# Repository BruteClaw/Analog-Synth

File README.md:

# Analog-Synth
Analog Synthasizer Designs

These are designs for EuroRack compatable synthasizer modules.

Each module is designed as a seperate project in KiCAD
Each folder includes a BOM from Mouser.com, the Gerber Files if you just want to have a board printed and a PDF of the schematic.

I have taken insparation from all over the web including Music From Outer Space, Yusynth and Look Mom no Computer.
Some designs are outright copies of their schematic with my board layout design.

Look in Overal Design.xlsx for where I have gotten the design from And current progress on the designs.

All designs are without waranty, please build at your own risk, I have not tested any of these designs at this time.
If you build any of them, you assume responsibiltiy for any potential damage to your existing equipment.

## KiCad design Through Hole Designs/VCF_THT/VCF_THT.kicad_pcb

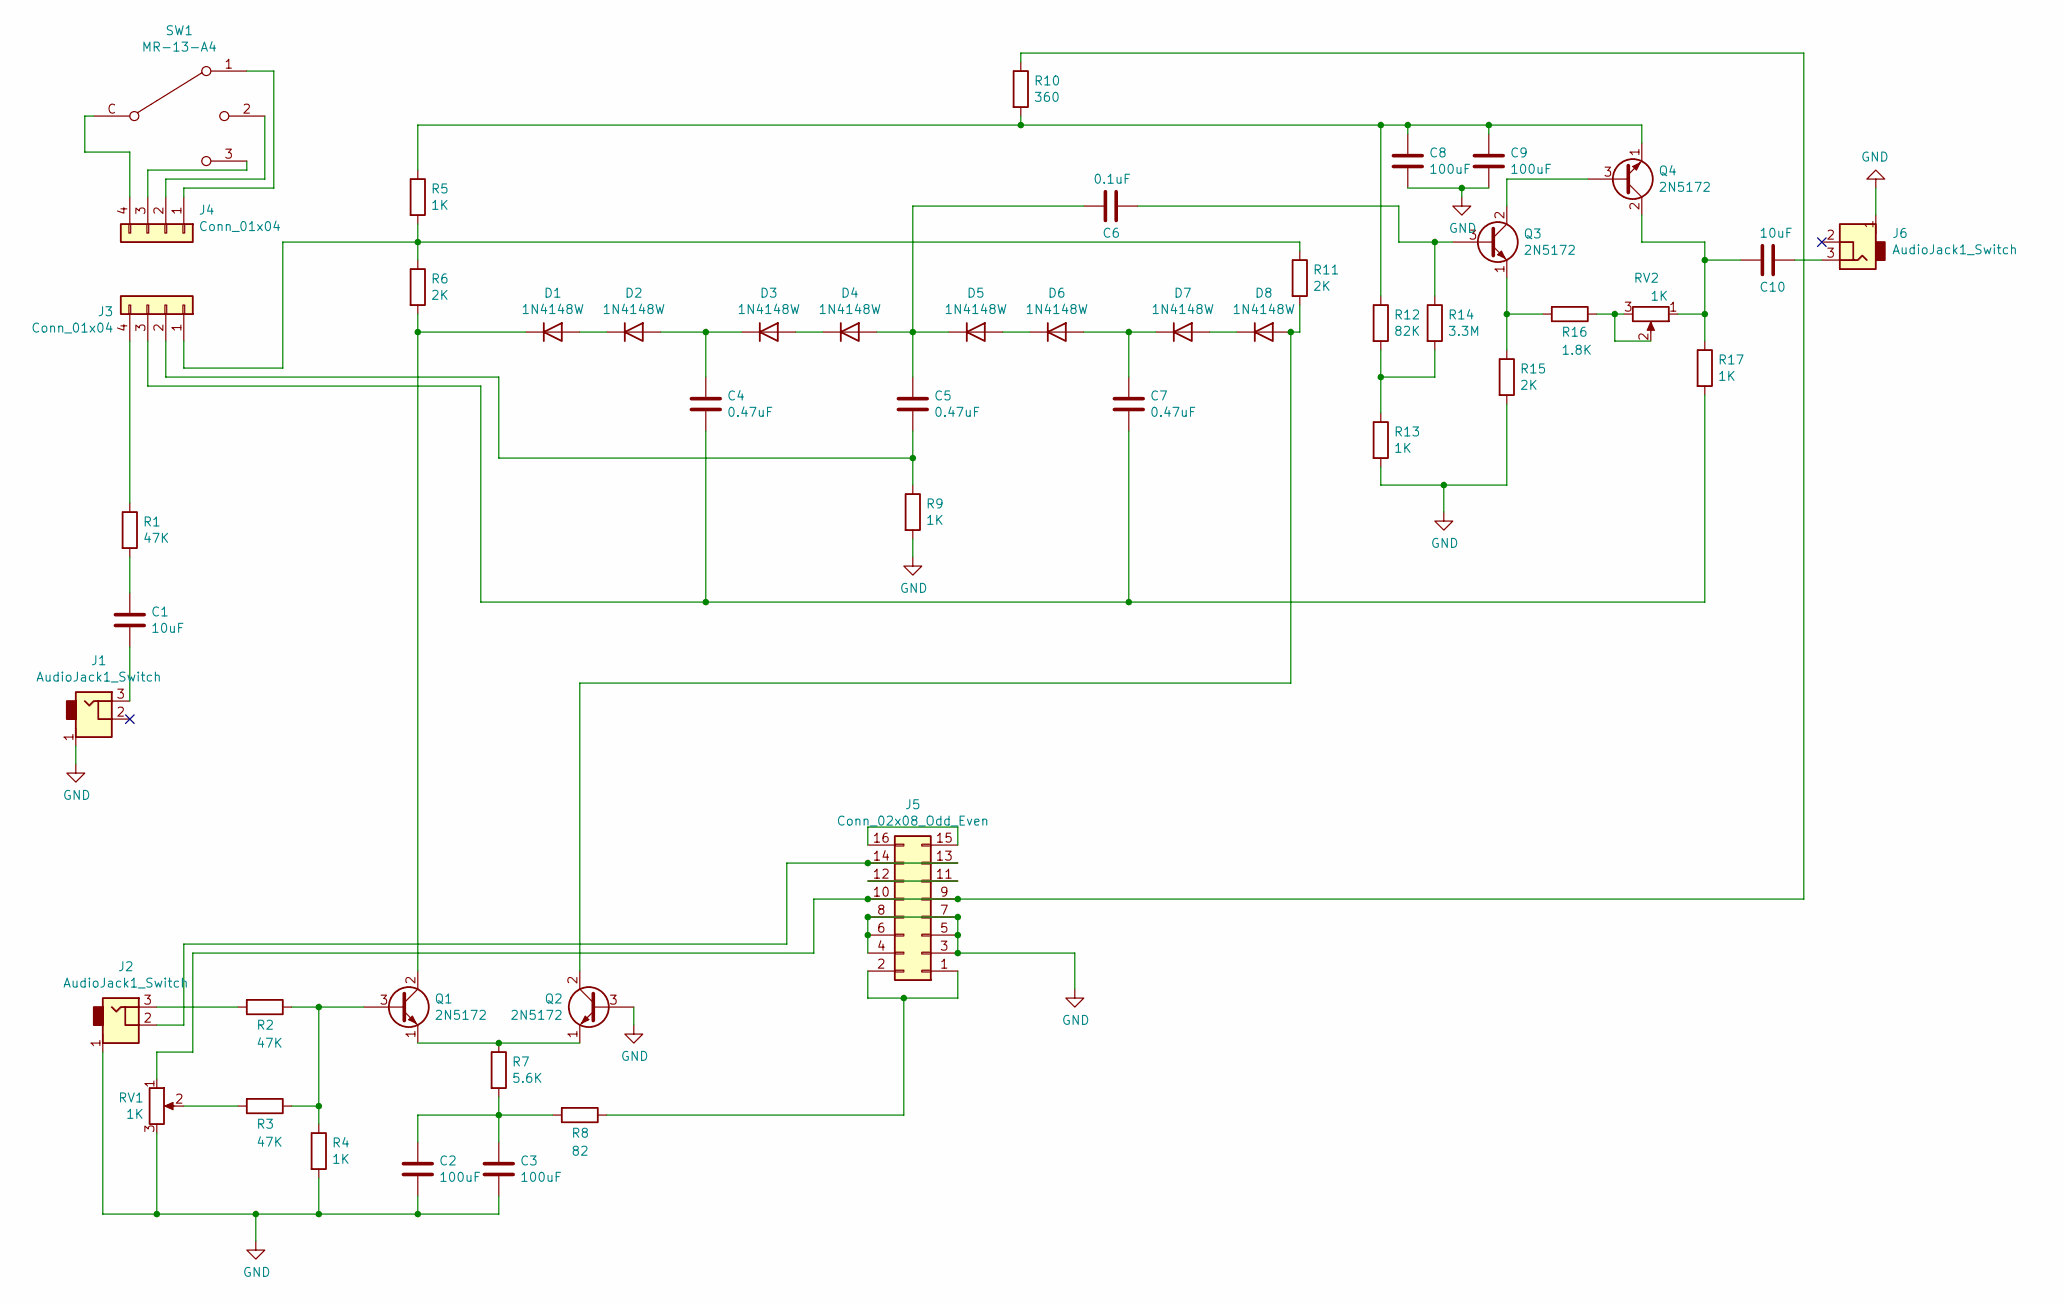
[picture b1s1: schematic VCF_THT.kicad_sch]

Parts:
C1, C10: 10uF; C_Disc_D5.0mm_W2.5mm_P2.50mm
C2, C3, C8, C9: 100uF; CP_Radial_D6.3mm_P2.50mm
C4, C5, C7: 0.47uF; C_Disc_D5.0mm_W2.5mm_P2.50mm
C6: 0.1uF; C_Disc_D5.0mm_W2.5mm_P2.50mm
D1, D2, D3, D4, D5, D6, D7, D8: 1N4148W; D_DO-35_SOD27_P7.62mm_Horizontal
J1, J2, J6: AudioJack1_Switch; Mono_Jack_3.5mm_Switch_Switchcraft_35RAPC2AH3
J3, J4: Conn_01x04; Pin_Header_Straight_1x04_Pitch2.54mm
J5: Conn_02x08_Odd_Even; Pin_Header_Straight_2x08_Pitch2.54mm
Q1, Q2, Q3, Q4: 2N5172; TO-92_Inline_Wide
R1, R2, R3: 47K; R_Axial_DIN0207_L6.3mm_D2.5mm_P10.16mm_Horizontal
R4, R5, R9, R13, R17: 1K; R_Axial_DIN0207_L6.3mm_D2.5mm_P10.16mm_Horizontal
R6, R11, R15: 2K; R_Axial_DIN0207_L6.3mm_D2.5mm_P10.16mm_Horizontal
R7: 5.6K; R_Axial_DIN0207_L6.3mm_D2.5mm_P10.16mm_Horizontal
R8: 82; R_Axial_DIN0207_L6.3mm_D2.5mm_P10.16mm_Horizontal
R10: 360; R_Axial_DIN0207_L6.3mm_D2.5mm_P10.16mm_Horizontal
R12: 82K; R_Axial_DIN0207_L6.3mm_D2.5mm_P10.16mm_Horizontal
R14: 3.3M; R_Axial_DIN0207_L6.3mm_D2.5mm_P10.16mm_Horizontal
R16: 1.8K; R_Axial_DIN0207_L6.3mm_D2.5mm_P10.16mm_Horizontal
RV1, RV2: 1K; Potentiometer_Bourns_PTV09A-2_Vertical
SW1: MR-13-A4

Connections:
GND: C2.2, C3.2, C8.2, C9.2, J1.1, J2.1, J5.3, J5.4, J5.5, J5.6, J5.7, J5.8, J6.1, Q2.3 (B), R4.2, R9.2, R13.2, R15.2, RV1.3
unnamed: C1.1, R1.2
unnamed: C1.2, J1.3
unnamed: C2.1, C3.1, R7.2, R8.2
unnamed: C4.1, D2.2 (A), D3.1 (K)
unnamed: C4.2, C7.2, J3.3, R17.2
unnamed: C5.1, C6.2, D4.2 (A), D5.1 (K)
unnamed: C5.2, J3.2, R9.1
unnamed: C6.1, Q3.3 (B), R14.1
unnamed: C7.1, D6.2 (A), D7.1 (K)
unnamed: C8.1, C9.1, Q4.1 (E), R5.1, R10.2, R12.1
unnamed: C10.1, J6.3
unnamed: C10.2, Q4.2 (C), R17.1, RV2.1
unnamed: D1.1 (K), Q1.2 (C), R6.2
unnamed: D1.2 (A), D2.1 (K)
unnamed: D3.2 (A), D4.1 (K)
unnamed: D5.2 (A), D6.1 (K)
unnamed: D7.2 (A), D8.1 (K)
unnamed: D8.2 (A), Q2.2 (C), R11.2
unnamed: J2.2, J5.13, J5.14
unnamed: J2.3, R2.2
unnamed: J3.1, R5.2, R6.1, R11.1
unnamed: J3.4, R1.1
unnamed: J4.1, SW1.1
unnamed: J4.2, SW1.2
unnamed: J4.3, SW1.3
unnamed: J4.4, SW1.C
unnamed: J5.1, J5.2, R8.1
unnamed: J5.9, J5.10, R10.1, RV1.1
unnamed: J5.11, J5.12
unnamed: J5.15, J5.16
unnamed: Q1.1 (E), Q2.1 (E), R7.1
unnamed: Q1.3 (B), R2.1, R3.1, R4.1
unnamed: Q3.1 (E), R15.1, R16.2
unnamed: Q3.2 (C), Q4.3 (B)
unnamed: R3.2, RV1.2
unnamed: R12.2, R13.1, R14.2
unnamed: R16.1, RV2.2, RV2.3

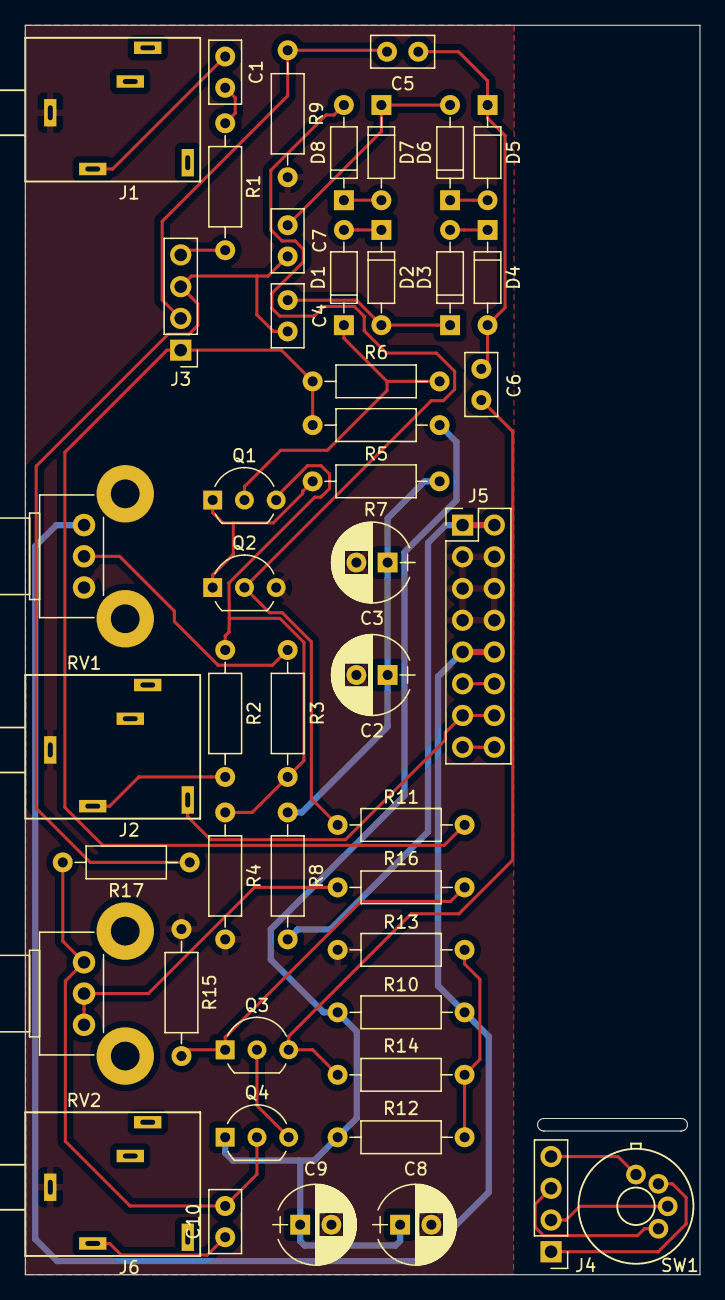
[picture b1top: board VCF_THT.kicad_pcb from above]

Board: 2 copper layers, 54.0 x 100.0 mm, 48 parts (0 on the bottom side), 38 nets.

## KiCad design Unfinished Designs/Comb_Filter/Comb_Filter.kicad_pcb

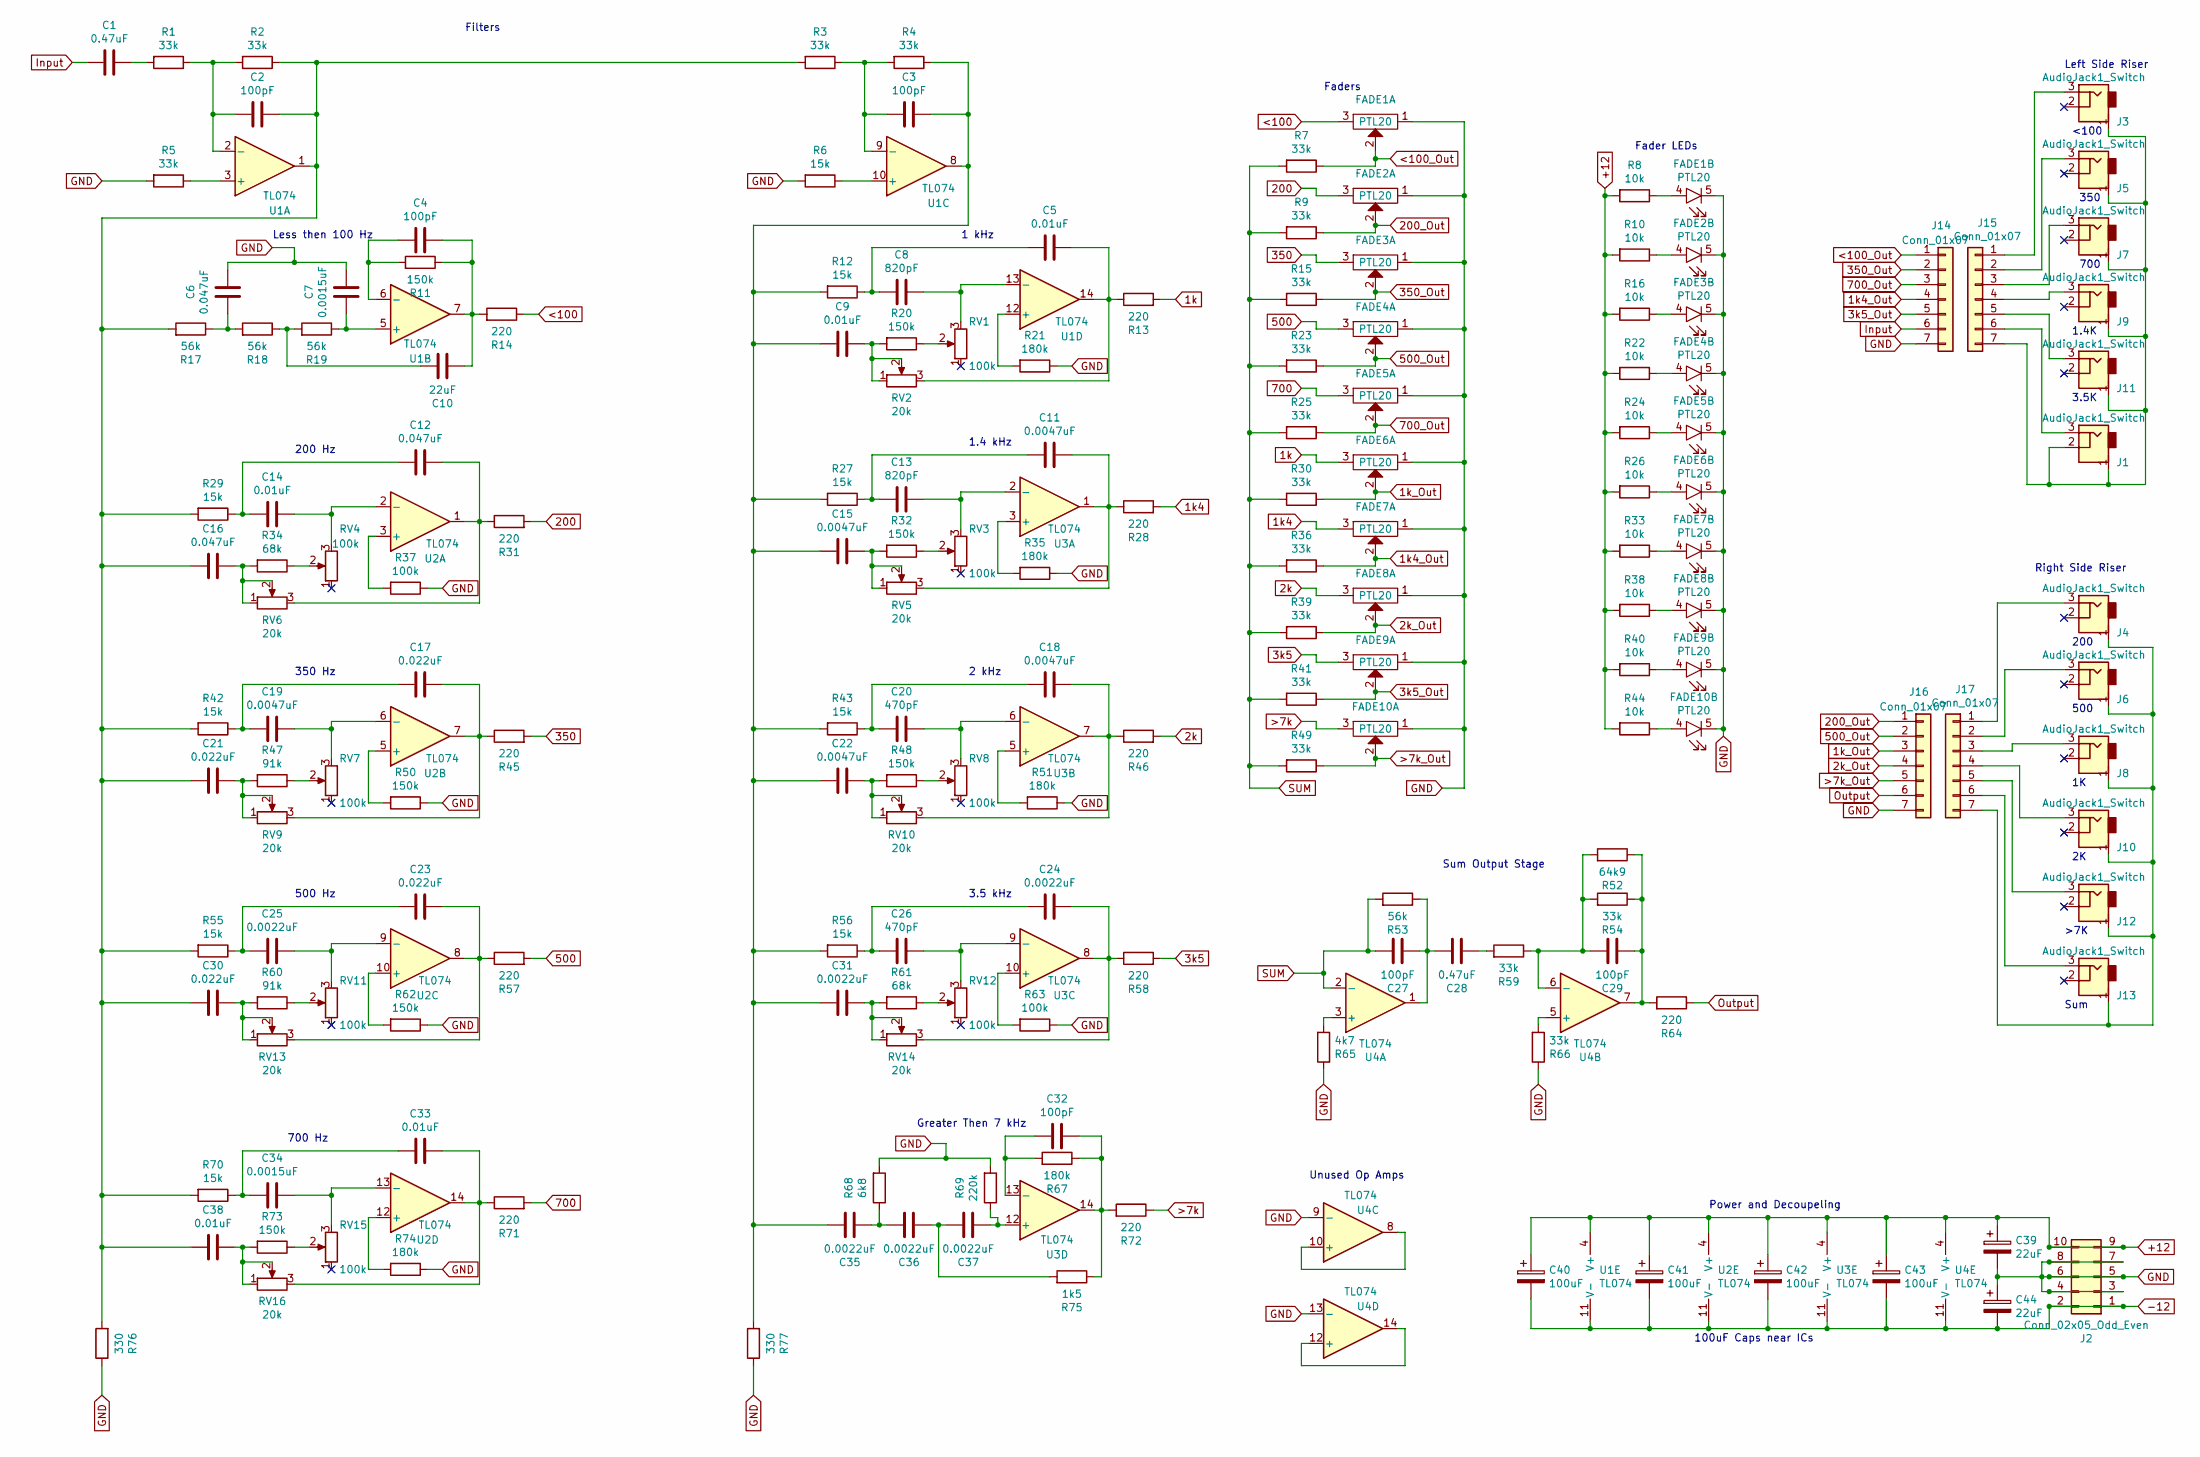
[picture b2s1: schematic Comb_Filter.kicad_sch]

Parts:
C1, C28: 0.47uF; C_1210_HandSoldering
C2, C3, C4, C27, C29, C32: 100pF; C_1210_HandSoldering
C5, C9, C14, C33, C38: 0.01uF; C_1210_HandSoldering
C6, C12, C16: 0.047uF; C_1210_HandSoldering
C7, C34: 0.0015uF; C_1210_HandSoldering
C8, C13: 820pF; C_1210_HandSoldering
C10: 22uF; C_1210_HandSoldering
C11, C15, C18, C19, C22: 0.0047uF; C_1210_HandSoldering
C17, C21, C23, C30: 0.022uF; C_1210_HandSoldering
C20, C26: 470pF; C_1210_HandSoldering
C24, C25, C31, C35, C36, C37: 0.0022uF; C_1210_HandSoldering
C39, C44: 22uF; CP_Elec_5x5.8
C40, C41, C42, C43: 100uF; CP_Elec_6.3x5.8
FADE1, FADE2, FADE3, FADE4, FADE5, FADE6, FADE7, FADE8, FADE9, FADE10: PTL20; PLT20
J1, J3, J4, J5, J6, J7, J8, J9, J10, J11, J12, J13: AudioJack1_Switch; Mono_Jack_3.5mm_Switch_Switchcraft_35RAPC2AH3
J2: Conn_02x05_Odd_Even; Pin_Header_Straight_2x05_Pitch2.54mm
J14, J15, J16, J17: Conn_01x07; Pin_Header_Straight_1x07_Pitch2.54mm
R1, R2, R3, R4, R5, R7, R9, R15, R23, R25, R30, R36, R39, R41, R49, R54, R59, R66: 33k; R_1210_HandSoldering
R6, R12, R27, R29, R42, R43, R55, R56, R70: 15k; R_1210_HandSoldering
R8, R10, R16, R22, R24, R26, R33, R38, R40, R44: 10k; R_1210_HandSoldering
R11, R20, R32, R48, R50, R62, R73: 150k; R_1210_HandSoldering
R13, R14, R28, R31, R45, R46, R57, R58, R64, R71, R72: 220; R_1210_HandSoldering
R17, R18, R19, R53: 56k; R_1210_HandSoldering
R21, R35, R51, R67, R74: 180k; R_1210_HandSoldering
R34, R61: 68k; R_1210_HandSoldering
R37, R63: 100k; R_1210_HandSoldering
R47, R60: 91k; R_1210_HandSoldering
R52: 64k9; R_1210_HandSoldering
R65: 4k7; R_1210_HandSoldering
R68: 6k8; R_1210_HandSoldering
R69: 220k; R_1210_HandSoldering
R75: 1k5; R_1210_HandSoldering
R76, R77: 330; R_1210_HandSoldering
RV1, RV3, RV4, RV7, RV8, RV11, RV12, RV15: 100k; PVG5A
RV2, RV5, RV6, RV9, RV10, RV13, RV14, RV16: 20k; PVG5A
U1, U2, U3, U4: TL074; SOIC-14_3.9x8.7mm_Pitch1.27mm

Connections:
1k: FADE6.3, R13.2
1k4: FADE7.3, R28.2
1k4_Out: FADE7.2, J14.4, R36.1
1k_Out: FADE6.2, J16.3, R30.1
2k: FADE8.3, R46.2
2k_Out: FADE8.2, J16.4, R39.1
3k5: FADE9.3, R58.2
3k5_Out: FADE9.2, J14.5, R41.1
200: FADE2.3, R31.2
200_Out: FADE2.2, J16.1, R9.1
350: FADE3.3, R45.2
350_Out: FADE3.2, J14.2, R15.1
500: FADE4.3, R57.2
500_Out: FADE4.2, J16.2, R23.1
700: FADE5.3, R71.2
700_Out: FADE5.2, J14.3, R25.1
+12: C39.1, C40.1, C41.1, C42.1, C43.1, J2.9, J2.10, R8.2, R10.2, R16.2, R22.2, R24.2, R26.2, R33.2, R38.2, R40.2, R44.2, U1.4 (V+), U2.4 (V+), U3.4 (V+), U4.4 (V+)
-12: C40.2, C41.2, C42.2, C43.2, C44.2, J2.1, J2.2, U1.11 (V-), U2.11 (V-), U3.11 (V-), U4.11 (V-)
<100: FADE1.3, R14.1
<100_Out: FADE1.2, J14.1, R7.1
>7k: FADE10.3, R72.1
>7k_Out: FADE10.2, J16.5, R49.1
GND: C6.2, C7.2, C39.2, C44.1, FADE1.1, FADE1.5 (E), FADE2.1, FADE2.5 (E), FADE3.1, FADE3.5 (E), FADE4.1, FADE4.5 (E), FADE5.1, FADE5.5 (E), FADE6.1, FADE6.5 (E), FADE7.1, FADE7.5 (E), FADE8.1, FADE8.5 (E), FADE9.1, FADE9.5 (E), FADE10.1, FADE10.5 (E), J2.3, J2.4, J2.5, J2.6, J2.7, J2.8, J14.7, J16.7, R5.2, R6.2, R21.1, R35.1, R37.1, R50.1, R51.1, R62.1, R63.1, R65.1, R66.1, R68.2, R69.2, R74.1, R76.1, R77.1, U4.9 (-), U4.13 (-)
Input: C1.2, J14.6
unnamed: C1.1, R1.2
unnamed: C2.2, R1.1, R2.2, U1.2 (-)
unnamed: C3.2, R3.1, R4.2, U1.9 (-)
unnamed: C4.1, R11.2, U1.6 (-)
unnamed: C5.1, R13.1, RV2.3, U1.14
unnamed: C5.2, C8.2, R12.1
unnamed: C6.1, R17.1, R18.2
unnamed: C7.1, R19.1, U1.5 (+)
unnamed: C8.1, RV1.3, U1.13 (-)
unnamed: C9.1, R20.2, RV2.1, RV2.2
unnamed: C4.2, C10.1, R11.1, R14.2, U1.7
unnamed: C10.2, R18.1, R19.2
unnamed: C11.1, R28.1, RV5.3, U3.1
unnamed: C11.2, C13.2, R27.1
unnamed: C12.1, R31.1, RV6.3, U2.1
unnamed: C12.2, C14.2, R29.1
unnamed: C13.1, RV3.3, U3.2 (-)
unnamed: C14.1, RV4.3, U2.2 (-)
unnamed: C15.1, R32.2, RV5.1, RV5.2
unnamed: C3.1, C9.2, C15.2, C22.2, C31.2, C35.2, R4.1, R12.2, R27.2, R43.2, R56.2, R77.2, U1.8
unnamed: C16.1, R34.2, RV6.1, RV6.2
unnamed: C2.1, C16.2, C21.2, C30.2, C38.2, R2.1, R3.2, R17.2, R29.2, R42.2, R55.2, R70.2, R76.2, U1.1
unnamed: C17.1, R45.1, RV9.3, U2.7
unnamed: C17.2, C19.2, R42.1
unnamed: C18.1, R46.1, RV10.3, U3.7
unnamed: C18.2, C20.2, R43.1
unnamed: C19.1, RV7.3, U2.6 (-)
unnamed: C20.1, RV8.3, U3.6 (-)
unnamed: C21.1, R47.2, RV9.1, RV9.2
unnamed: C22.1, R48.2, RV10.1, RV10.2
unnamed: C23.1, R57.1, RV13.3, U2.8
unnamed: C23.2, C25.2, R55.1
unnamed: C24.1, R58.1, RV14.3, U3.8
unnamed: C24.2, C26.2, R56.1
unnamed: C25.1, RV11.3, U2.9 (-)
unnamed: C26.1, RV12.3, U3.9 (-)
unnamed: C27.1, C28.2, R53.1, U4.1
unnamed: C28.1, R59.2
unnamed: C29.1, R52.1, R54.1, R64.2, U4.7
unnamed: C29.2, R52.2, R54.2, R59.1, U4.6 (-)
unnamed: C30.1, R60.2, RV13.1, RV13.2
unnamed: C31.1, R61.2, RV14.1, RV14.2
unnamed: C32.1, R67.2, U3.13 (-)
unnamed: C32.2, R67.1, R72.2, R75.1, U3.14
unnamed: C33.1, R71.1, RV16.3, U2.14
unnamed: C33.2, C34.2, R70.1
unnamed: C34.1, RV15.3, U2.13 (-)
unnamed: C35.1, C36.2, R68.1
unnamed: C36.1, C37.2, R75.2
unnamed: C37.1, R69.1, U3.12 (+)
unnamed: C38.1, R73.2, RV16.1, RV16.2
unnamed: FADE1.4 (B), R8.1
unnamed: FADE2.4 (B), R10.1
unnamed: FADE3.4 (B), R16.1
unnamed: FADE4.4 (B), R22.1
unnamed: FADE5.4 (B), R24.1
unnamed: FADE6.4 (B), R26.1
unnamed: FADE7.4 (B), R33.1
unnamed: FADE8.4 (B), R38.1
unnamed: FADE9.4 (B), R40.1
unnamed: FADE10.4 (B), R44.1
unnamed: J1.1, J1.2, J3.1, J5.1, J7.1, J9.1, J11.1, J15.7
unnamed: J1.3, J15.6
unnamed: J4.1, J6.1, J8.1, J10.1, J12.1, J13.1, J17.7
unnamed: J10.3, J17.4
unnamed: J11.3, J15.5
unnamed: J12.3, J17.5
unnamed: J13.3, J17.6
unnamed: J3.3, J15.1
unnamed: J5.3, J15.2
unnamed: J7.3, J15.3
unnamed: J9.3, J15.4
unnamed: J4.3, J17.1
unnamed: J6.3, J17.2
unnamed: J8.3, J17.3
unnamed: R5.1, U1.3 (+)
unnamed: R6.1, U1.10 (+)
unnamed: R20.1, RV1.2
unnamed: R21.2, U1.12 (+)
unnamed: R32.1, RV3.2
unnamed: R34.1, RV4.2
unnamed: R35.2, U3.3 (+)
unnamed: R37.2, U2.3 (+)
unnamed: R47.1, RV7.2
unnamed: R48.1, RV8.2
unnamed: R50.2, U2.5 (+)
unnamed: R51.2, U3.5 (+)
unnamed: R60.1, RV11.2
unnamed: R61.1, RV12.2
unnamed: R62.2, U2.10 (+)
unnamed: R63.2, U3.10 (+)
unnamed: R65.2, U4.3 (+)
unnamed: R66.2, U4.5 (+)
unnamed: R73.1, RV15.2
unnamed: R74.2, U2.12 (+)
unnamed: U4.8, U4.10 (+)
unnamed: U4.12 (+), U4.14
Output: J16.6, R64.1
SUM: C27.2, R7.2, R9.2, R15.2, R23.2, R25.2, R30.2, R36.2, R39.2, R41.2, R49.2, R53.2, U4.2 (-)

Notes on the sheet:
Faders
500 Hz
350
Unused Op Amps
350 Hz
Left Side Riser
Sum Output Stage
>7K
500
3.5 kHz
1.4 kHz
1.4K
200 Hz
Fader LEDs
Greater Then 7 kHz
2 kHz
3.5K
Right Side Riser
Filters
Less then 100 Hz
<100
700 Hz
1 kHz
Sum
700
200
Power and Decoupeling
100uF Caps near ICs

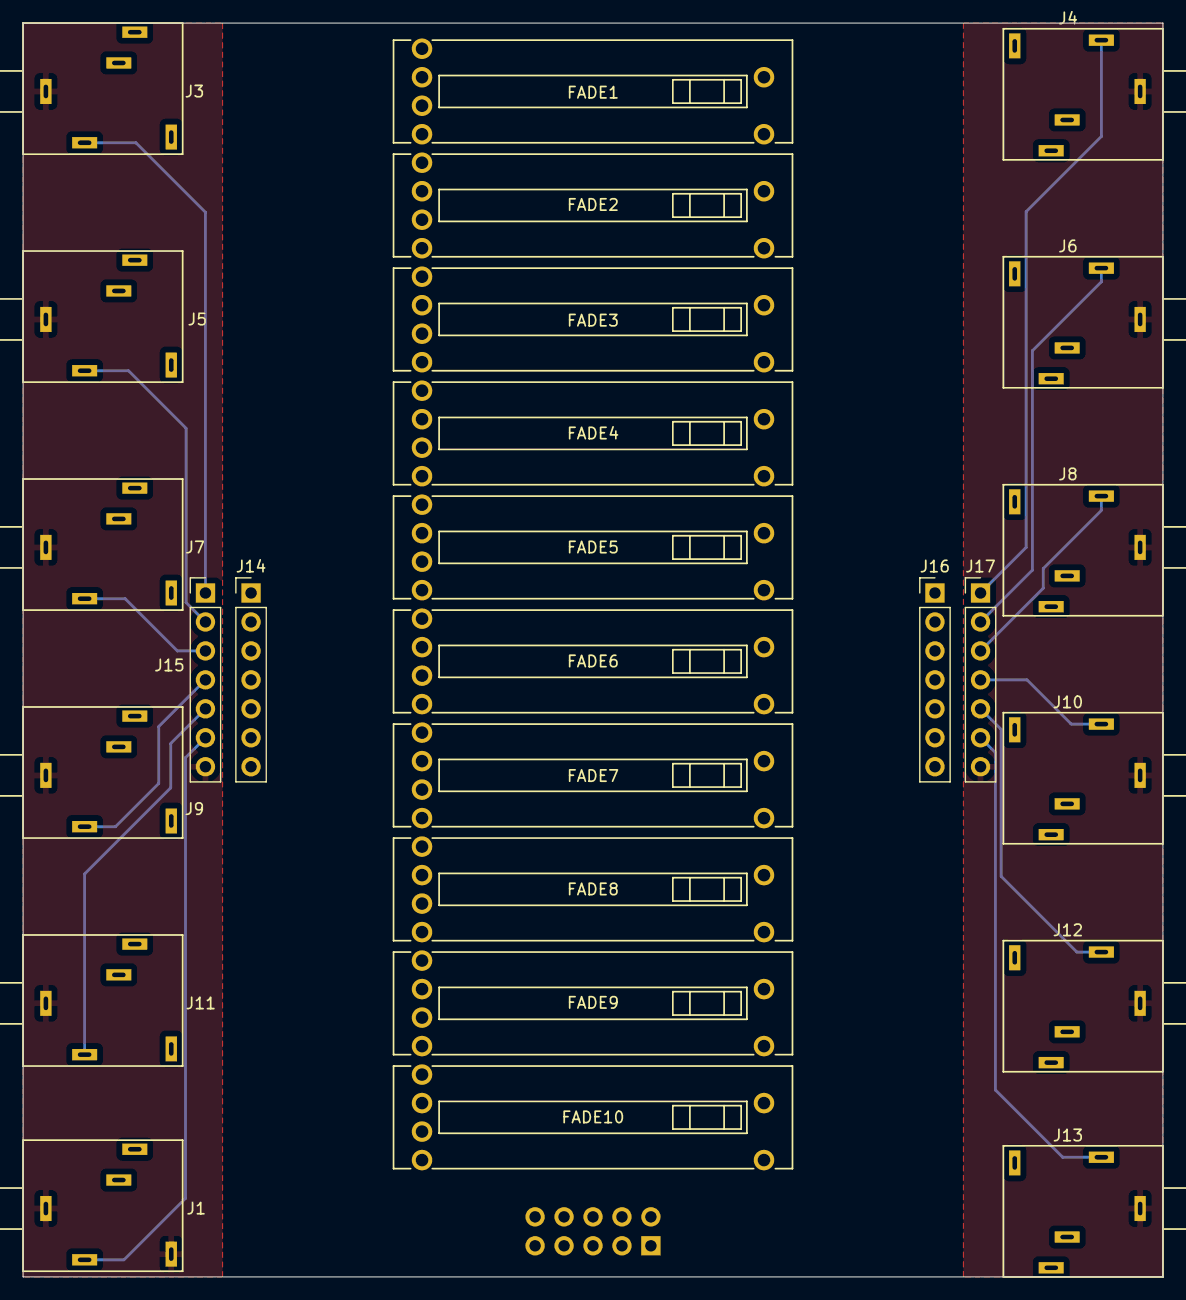
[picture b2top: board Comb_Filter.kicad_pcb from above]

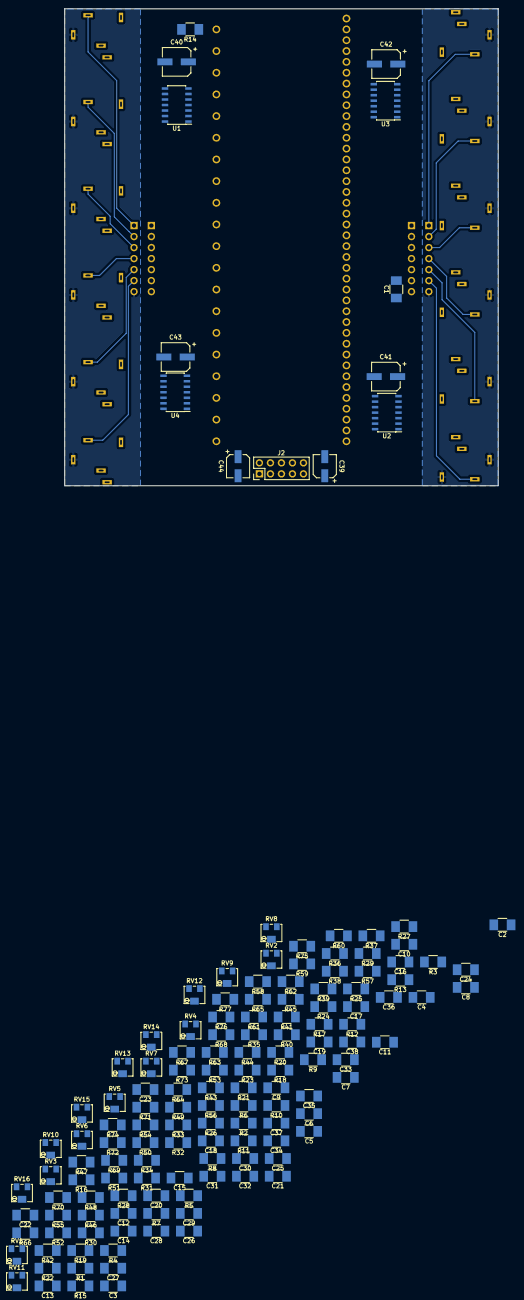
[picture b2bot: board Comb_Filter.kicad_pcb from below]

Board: 2 copper layers, 100.0 x 110.0 mm, 168 parts (142 on the bottom side), 123 nets.

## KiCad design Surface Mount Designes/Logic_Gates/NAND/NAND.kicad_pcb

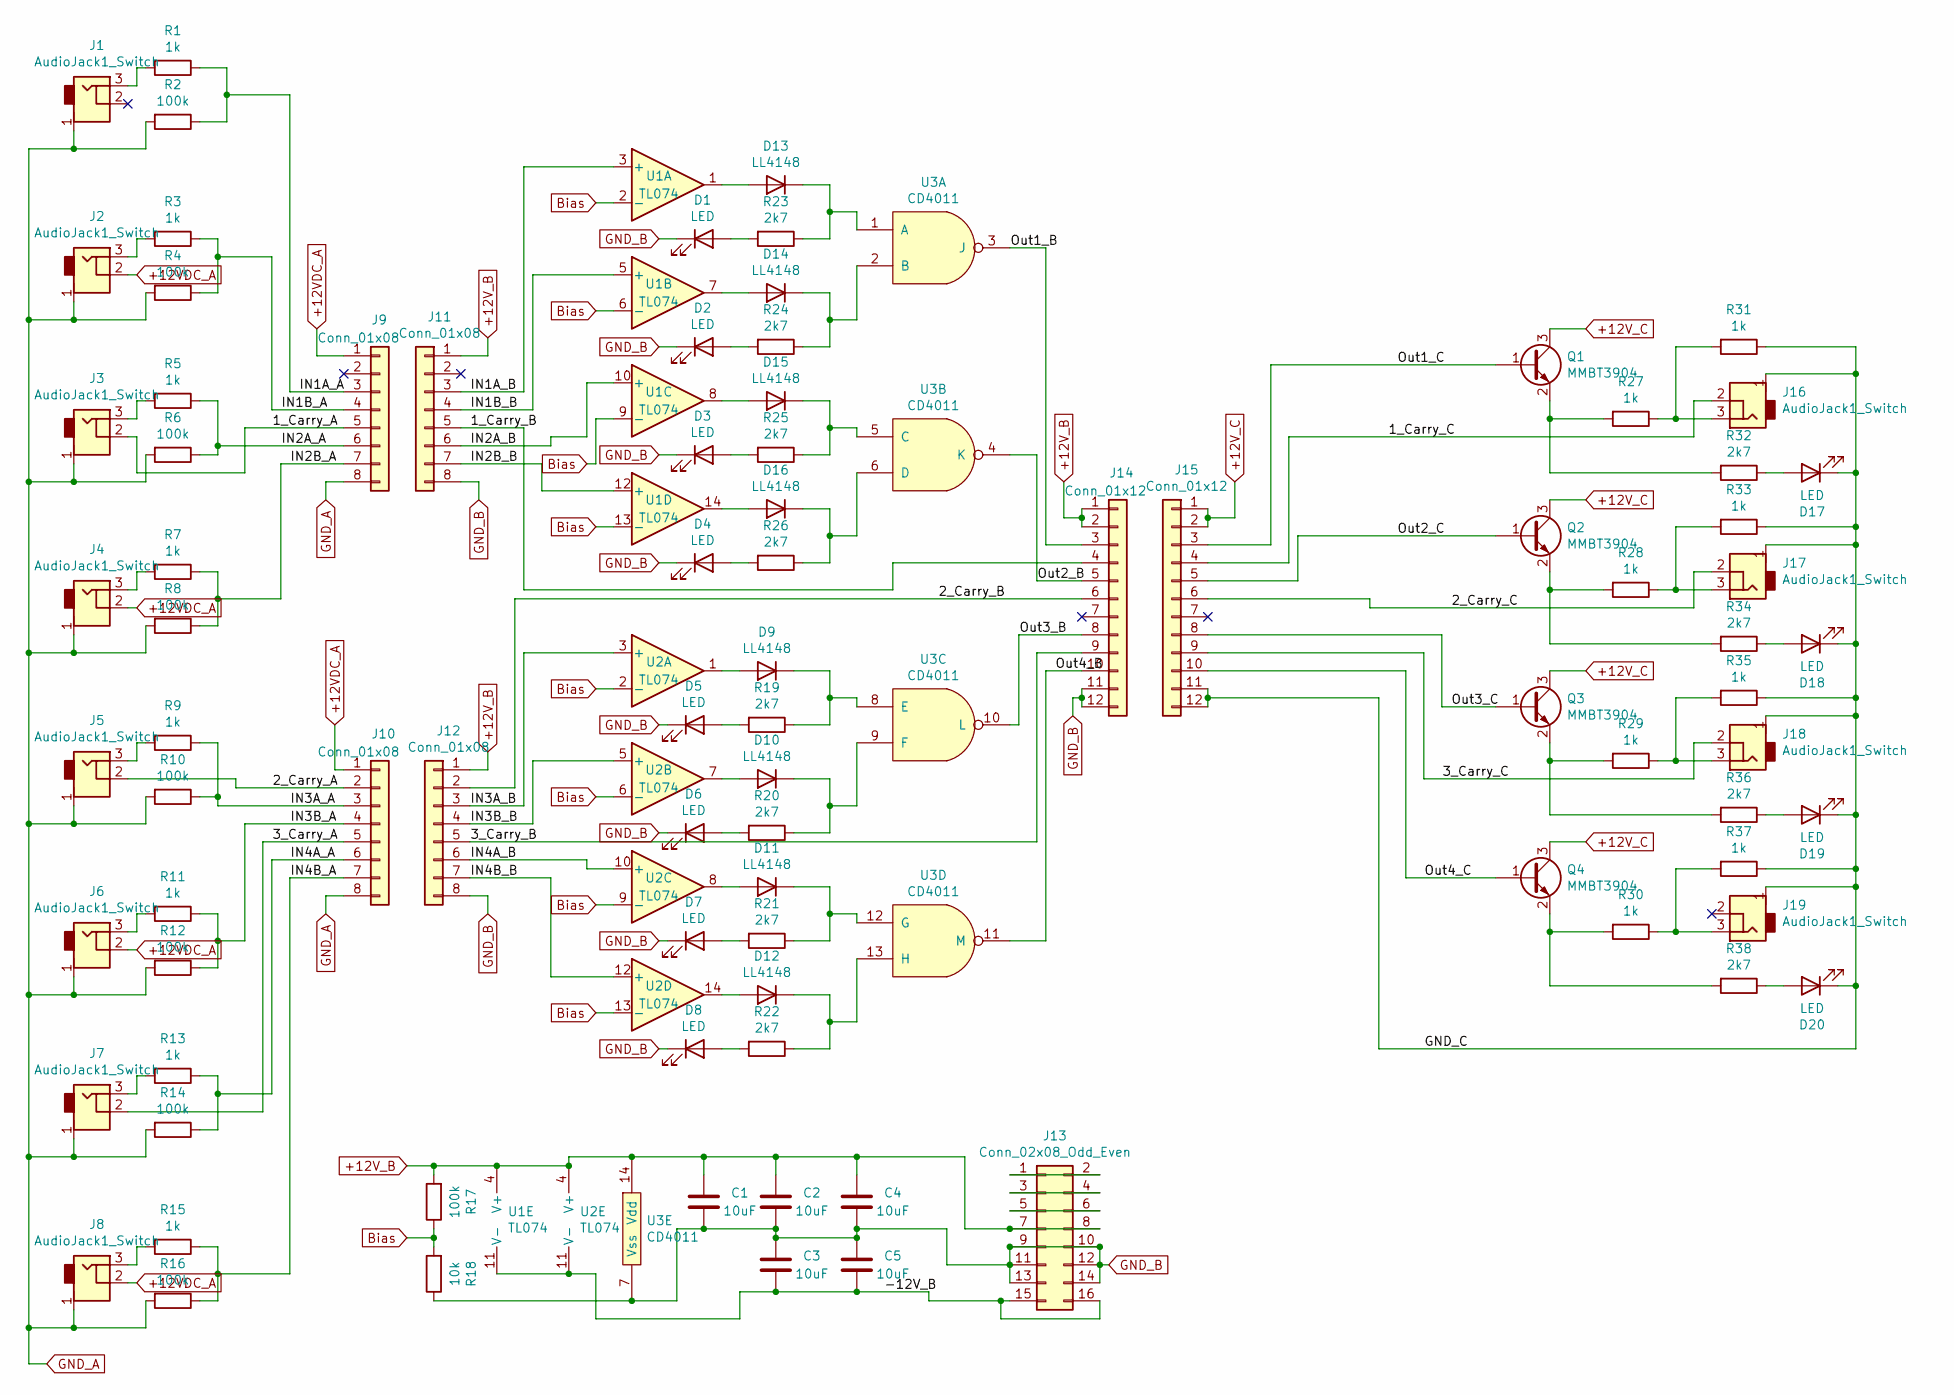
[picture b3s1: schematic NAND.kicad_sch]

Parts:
C1, C2, C3, C4, C5: 10uF; C_1210_HandSoldering
D1, D2, D3, D4, D5, D6, D7, D8, D17, D18, D19, D20: LED; LED_Rectangular_W3.9mm_H1.9mm
D9, D10, D11, D12, D13, D14, D15, D16: LL4148; D_MiniMELF_Handsoldering
J1, J2, J3, J4, J5, J6, J7, J8, J16, J17, J18, J19: AudioJack1_Switch; Mono_Jack_3.5mm_Switch_Switchcraft_35RAPC2AH3
J9, J10, J11, J12: Conn_01x08; Pin_Header_Straight_1x08_Pitch2.54mm
J13: Conn_02x08_Odd_Even; Pin_Header_Straight_2x08_Pitch2.54mm
J14, J15: Conn_01x12; Pin_Header_Straight_1x12_Pitch2.54mm
Q1, Q2, Q3, Q4: MMBT3904; SOT-23
R1, R3, R5, R7, R9, R11, R13, R15, R27, R28, R29, R30, R31, R33, R35, R37: 1k; R_1210_HandSoldering
R2, R4, R6, R8, R10, R12, R14, R16, R17: 100k; R_1210_HandSoldering
R18: 10k; R_1210_HandSoldering
R19, R20, R21, R22, R23, R24, R25, R26, R32, R34, R36, R38: 2k7; R_1210_HandSoldering
U1, U2: TL074; SOIC-14_3.9x8.7mm_Pitch1.27mm
U3: CD4011; SOIC-14_3.9x8.7mm_Pitch1.27mm

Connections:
+12VDC_A: J2.2, J4.2, J6.2, J8.2, J9.1, J10.1
+12V_B: C1.2, C2.2, C4.2, J11.1, J12.1, J13.7, J13.8, J14.1, J14.2, R17.2, U1.4 (V+), U2.4 (V+), U3.14 (Vdd)
+12V_C: J15.1, J15.2, Q1.3 (C), Q2.3 (C), Q3.3 (C), Q4.3 (C)
/1_Carry_A: J3.2, J9.5
/1_Carry_B: J11.5, J14.4
/1_Carry_C: J15.4, J16.2
/2_Carry_A: J5.2, J10.2
/2_Carry_B: J12.2, J14.6
/2_Carry_C: J15.6, J17.2
/3_Carry_A: J7.2, J10.5
/3_Carry_B: J12.5, J14.9
/3_Carry_C: J15.9, J18.2
/-12V_B: C3.1, C5.1, J13.15, J13.16, U1.11 (V-), U2.11 (V-)
/GND_C: D17.1 (K), D18.1 (K), D19.1 (K), D20.1 (K), J15.11, J15.12, J16.1, J17.1, J18.1, J19.1, R31.1, R33.1, R35.1, R37.1
/IN1A_A: J9.3, R1.1, R2.1
/IN1A_B: J11.3, U1.3 (+)
/IN1B_A: J9.4, R3.1, R4.1
/IN1B_B: J11.4, U1.5 (+)
/IN2A_A: J9.6, R5.1, R6.1
/IN2A_B: J11.6, U1.10 (+)
/IN2B_A: J9.7, R7.1, R8.1
/IN2B_B: J11.7, U1.12 (+)
/IN3A_A: J10.3, R9.1, R10.1
/IN3A_B: J12.3, U2.3 (+)
/IN3B_A: J10.4, R11.1, R12.1
/IN3B_B: J12.4, U2.5 (+)
/IN4A_A: J10.6, R13.1, R14.1
/IN4A_B: J12.6, U2.10 (+)
/IN4B_A: J10.7, R15.1, R16.1
/IN4B_B: J12.7, U2.12 (+)
/Out1_B: J14.3, U3.3 (J)
/Out1_C: J15.3, Q1.1 (B)
/Out2_B: J14.5, U3.4 (K)
/Out2_C: J15.5, Q2.1 (B)
/Out3_B: J14.8, U3.10 (L)
/Out3_C: J15.8, Q3.1 (B)
/Out4_B: J14.10, U3.11 (M)
/Out4_C: J15.10, Q4.1 (B)
Bias: R17.1, R18.2, U1.2 (-), U1.6 (-), U1.9 (-), U1.13 (-), U2.2 (-), U2.6 (-), U2.9 (-), U2.13 (-)
GND_A: J1.1, J2.1, J3.1, J4.1, J5.1, J6.1, J7.1, J8.1, J9.8, J10.8, R2.2, R4.2, R6.2, R8.2, R10.2, R12.2, R14.2, R16.2
GND_B: C1.1, C2.1, C3.2, C4.1, C5.2, D1.1 (K), D2.1 (K), D3.1 (K), D4.1 (K), D5.1 (K), D6.1 (K), D7.1 (K), D8.1 (K), J11.8, J12.8, J13.9, J13.10, J13.11, J13.12, J13.13, J13.14, J14.11, J14.12, R18.1, U3.7 (Vss)
unnamed: D1.2 (A), R23.2
unnamed: D2.2 (A), R24.2
unnamed: D3.2 (A), R25.2
unnamed: D4.2 (A), R26.2
unnamed: D5.2 (A), R19.2
unnamed: D6.2 (A), R20.2
unnamed: D7.2 (A), R21.2
unnamed: D8.2 (A), R22.2
unnamed: D9.1 (K), R19.1, U3.8 (E)
unnamed: D9.2 (A), U2.1
unnamed: D10.1 (K), R20.1, U3.9 (F)
unnamed: D10.2 (A), U2.7
unnamed: D11.1 (K), R21.1, U3.12 (G)
unnamed: D11.2 (A), U2.8
unnamed: D12.1 (K), R22.1, U3.13 (H)
unnamed: D12.2 (A), U2.14
unnamed: D13.1 (K), R23.1, U3.1 (A)
unnamed: D13.2 (A), U1.1
unnamed: D14.1 (K), R24.1, U3.2 (B)
unnamed: D14.2 (A), U1.7
unnamed: D15.1 (K), R25.1, U3.5 (C)
unnamed: D15.2 (A), U1.8
unnamed: D16.1 (K), R26.1, U3.6 (D)
unnamed: D16.2 (A), U1.14
unnamed: D17.2 (A), R32.1
unnamed: D18.2 (A), R34.1
unnamed: D19.2 (A), R36.1
unnamed: D20.2 (A), R38.1
unnamed: J1.3, R1.2
unnamed: J2.3, R3.2
unnamed: J3.3, R5.2
unnamed: J4.3, R7.2
unnamed: J5.3, R9.2
unnamed: J6.3, R11.2
unnamed: J7.3, R13.2
unnamed: J8.3, R15.2
unnamed: J13.1, J13.2
unnamed: J13.3, J13.4
unnamed: J13.5, J13.6
unnamed: J16.3, R27.1, R31.2
unnamed: J17.3, R28.1, R33.2
unnamed: J18.3, R29.1, R35.2
unnamed: J19.3, R30.1, R37.2
unnamed: Q1.2 (E), R27.2, R32.2
unnamed: Q2.2 (E), R28.2, R34.2
unnamed: Q3.2 (E), R29.2, R36.2
unnamed: Q4.2 (E), R30.2, R38.2

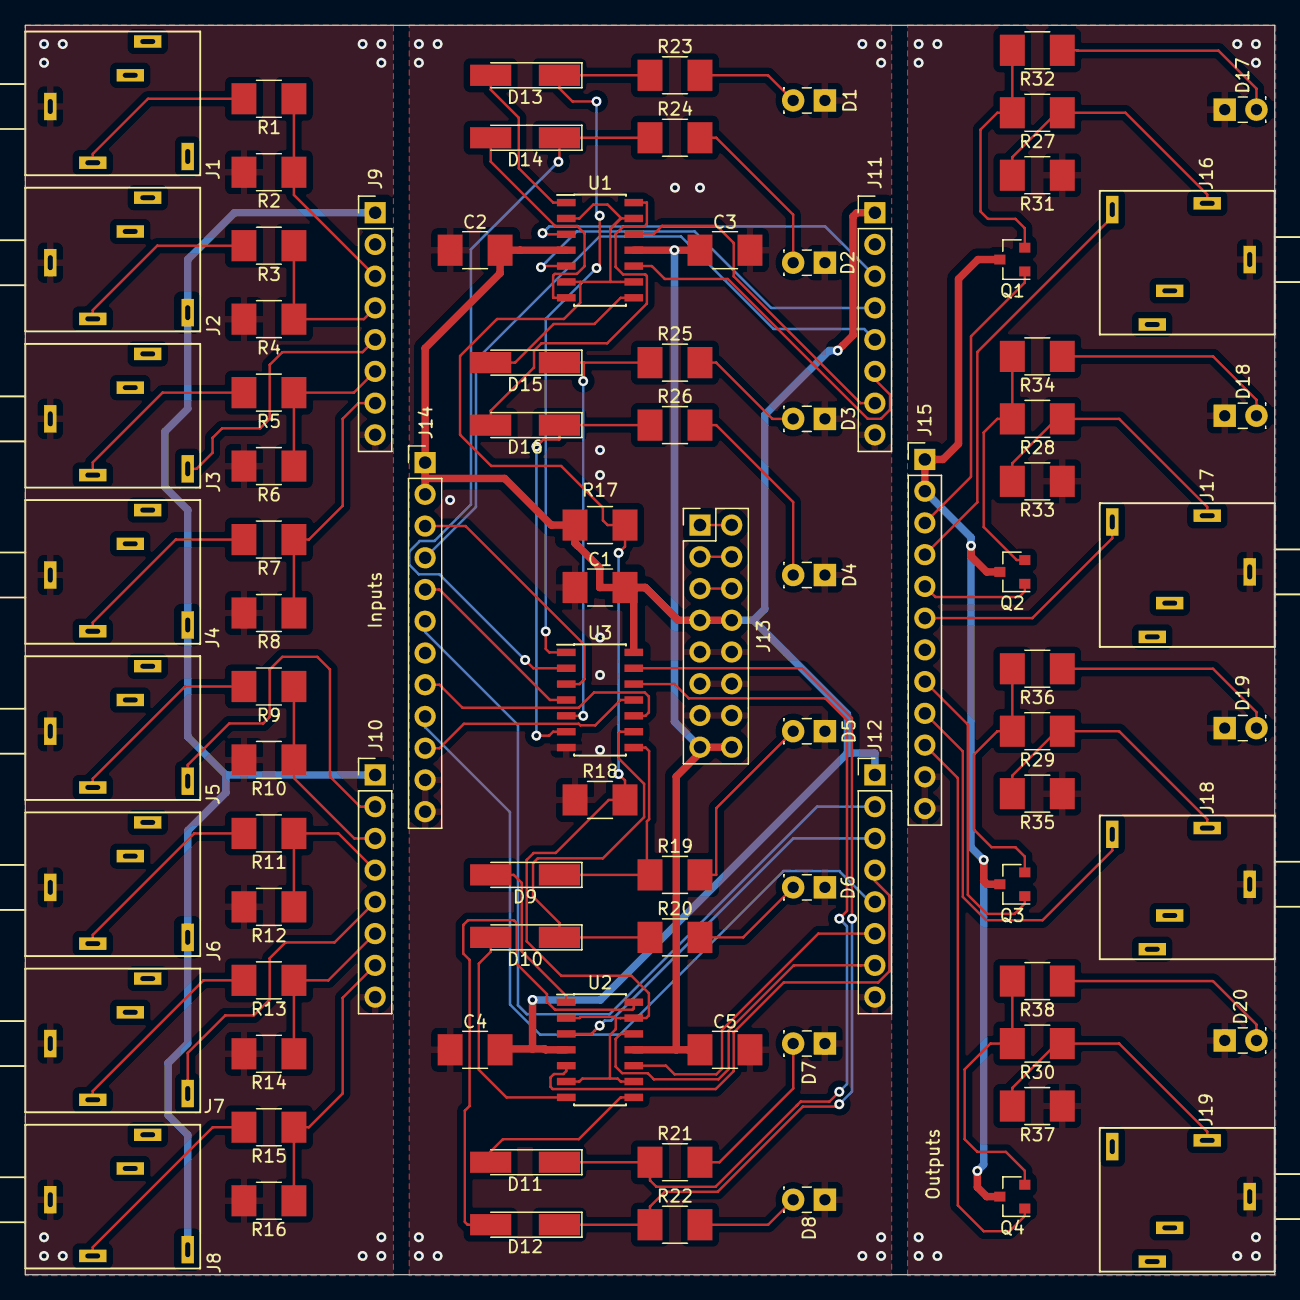
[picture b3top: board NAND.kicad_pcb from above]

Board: 2 copper layers, 100.0 x 100.0 mm, 89 parts (0 on the bottom side), 88 nets.
